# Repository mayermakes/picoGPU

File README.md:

# picoGPU
RPi pico used as crude Graphics adapter (only low res text mode)

Firmware for RP2040/pico
-> can receive commands via I2C and SERIAL
i2c allows for more screen control ( only works between MCUs for unknown reason)
Serial just prints what it receives to screen and changes to random color for each new page.
Serial works on MCu and SBC/PC

Driver published as python script and compiled binary for Linux (x86_AMD64 and RPI_ARM).
For those asking for a windows exe..... pffffff...lol

Seriously, pray that I never get the urge to publish special exe files. 
Meanwhile you can use a windows machine to compile the python script into an exe.

as seen on Element14 presents 2024
CC-BY-SA mayermakes 2024
 MAYER MAKES in all varaiants are registered trademarks.
Raspberry PI and any other Trademarks belong to their respective owners.

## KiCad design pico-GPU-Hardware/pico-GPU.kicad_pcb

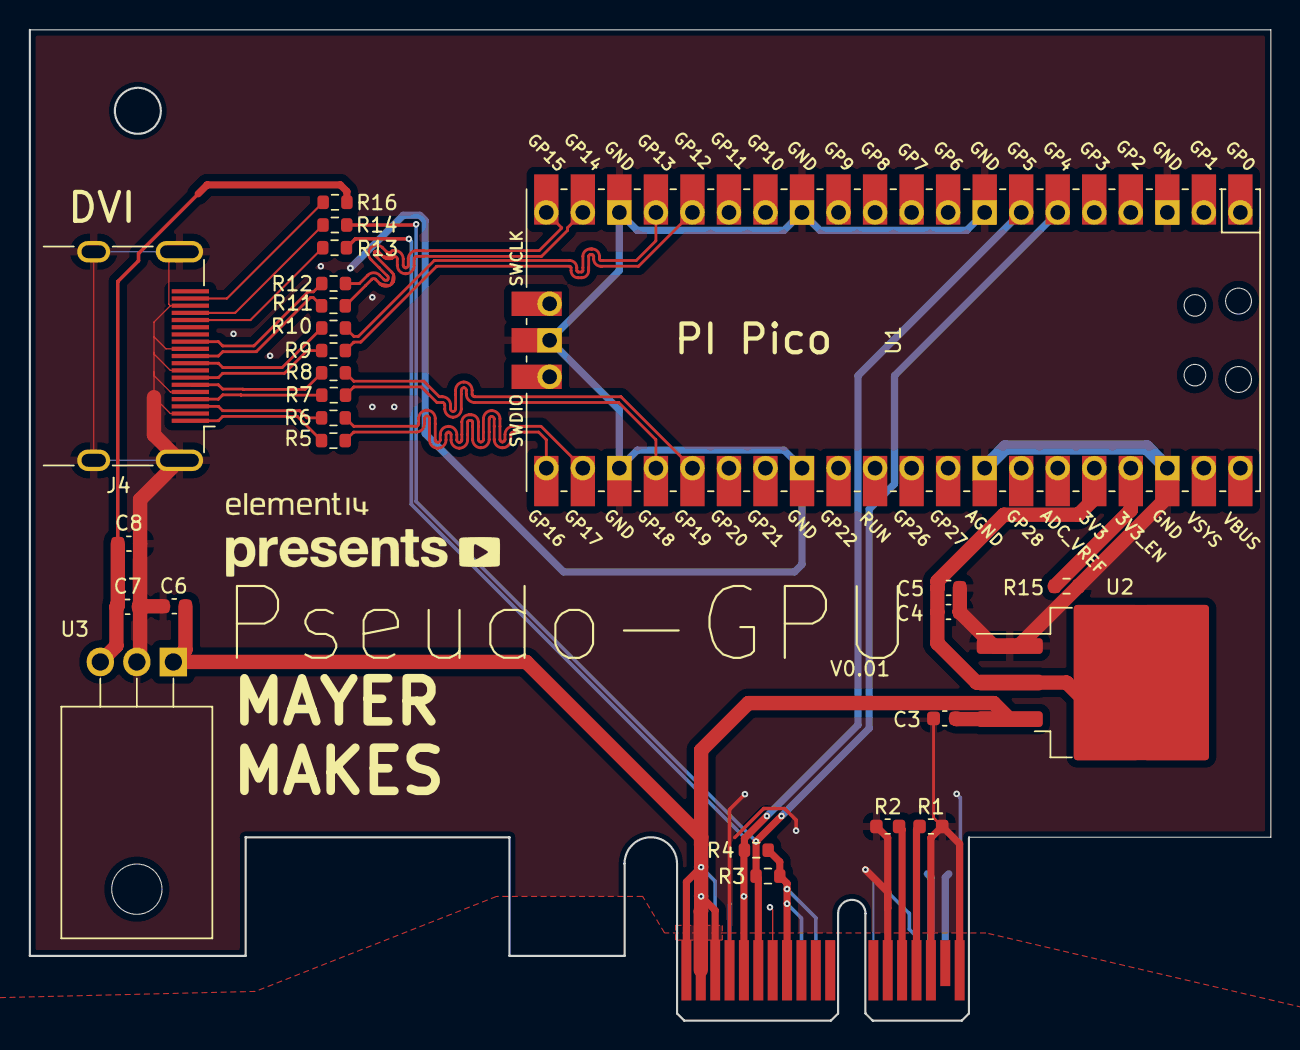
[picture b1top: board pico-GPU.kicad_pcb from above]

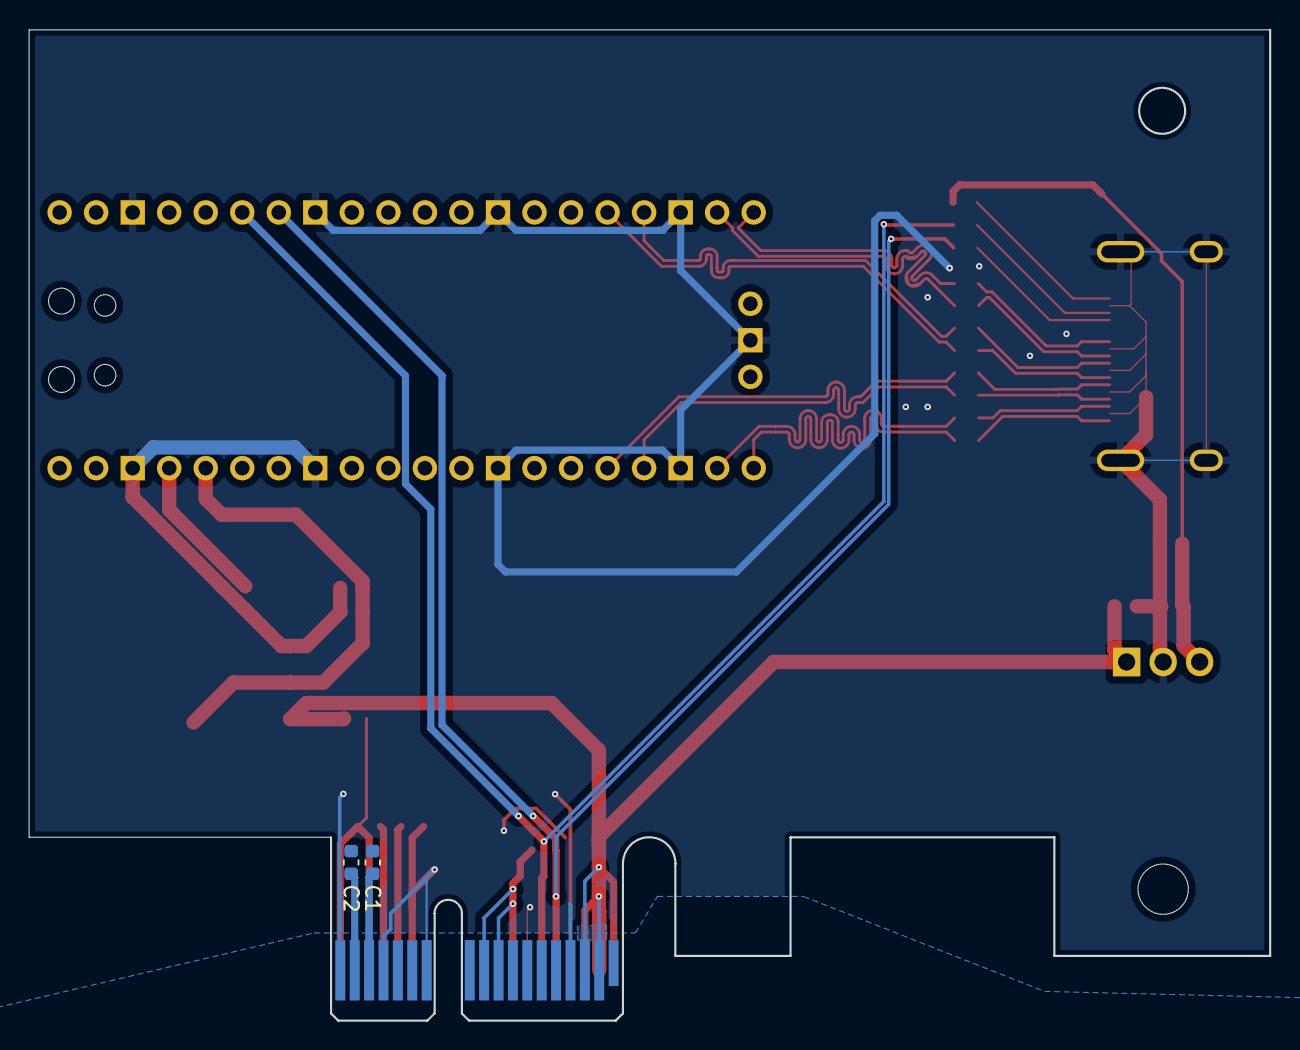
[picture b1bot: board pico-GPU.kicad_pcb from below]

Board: 2 copper layers, 86.2 x 68.9 mm, 31 parts (2 on the bottom side), 31 nets.

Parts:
C1, C2: 100n; C_0603_1608Metric
C3, C4, C6, C7: 10uF; C_0603_1608Metric
C5, C8: 0,1uF; C_0603_1608Metric
J1: PCIexpress_bracket; PCIexpress_bracket_full
J2: PCIexpress_x1
J4: NOT_HDMI_A; HDMI_A_Molex_208658-1001_Horizontal
R1, R2: 49.9; R_0603_1608Metric
R3, R4: 100k; R_0603_1608Metric
R5, R6, R7, R8, R9, R10, R11, R12: 270; R_0603_1608Metric
R13, R14, R15, R16: 0; R_0603_1608Metric
Ref**: Val**; e14presents logo 20mm silk only v1
U1: Pico; RPi_Pico_SMD_TH
U2: LM1085-3.3; TO-263-3_TabPin2
U3: LM7805_TO220; TO-220F-3_Horizontal_TabDown

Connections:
3V3_RAIL: C4.1, C5.1, U1.36 (3V3), U2.2 (VO)
5V_RAIL: C7.1, C8.1, R16.1, U3.3 (VO)
+3V3: J2.A9 (+3.3V), J2.A10 (+3.3V), J2.B8 (+3.3V), R3.1, R4.1
+12V: C3.1, C6.1, J2.A2 (+12V), J2.A3 (+12V), J2.B1 (+12V), J2.B2 (+12V), J2.B3 (+12V), U2.3 (VI), U3.1 (VI)
/CK+: J4.10 (CK+), R11.2
/CK-: J4.12 (CK-), R12.2
/D0+: J4.7 (D0+), R9.2
/D0-: J4.9 (D0-), R10.2
/D1+: J4.4 (D1+), R7.2
/D1-: J4.6 (D1-), R8.2
/D2+: J4.1 (D2+), R5.2
/D2-: J4.3 (D2-), R6.2
/PCIexpress_connector/_PER0_N: C2.1, J2.A17 (PERn0)
/PCIexpress_connector/_PER0_P: C1.2, J2.A16 (PERp0)
/PET0_N: J2.B15 (PETn0), R1.1
/PET0_P: J2.B14 (PETp0), R2.1
/PICO_CK+: R11.1, U1.19 (GPIO14)
/PICO_CK-: R12.1, U1.20 (GPIO15)
/PICO_D0+: R9.1, U1.16 (GPIO12)
/PICO_D0-: R10.1, U1.17 (GPIO13)
/PICO_D1+: R7.1, U1.24 (GPIO18)
/PICO_D1-: R8.1, U1.25 (GPIO19)
/PICO_D2+: R5.1, U1.21 (GPIO16)
/PICO_D2-: R6.1, U1.22 (GPIO17)
/SMCLK: J2.B5 (SMCLK), R4.2, R13.1, U1.7 (GPIO5)
/SMDAT: J2.B6 (SMDAT), R3.2, R14.1, U1.6 (GPIO4)
GND: C3.2, C4.2, C5.2, C6.2, C7.2, C8.2, J2.A4 (GND), J2.A12 (GND), J2.A15 (GND), J2.A18 (GND), J2.B4 (GND), J2.B7 (GND), J2.B13 (GND), J2.B16 (GND), J2.B18 (GND), J4.2 (D2S), J4.5 (D1S), J4.8 (D0S), J4.11 (CKS), J4.17 (GND), J4.SH, R1.2, R2.2, R15.2, U1.3 (GND), U1.8 (GND), U1.13 (GND), U1.18 (GND), U1.23 (GND), U1.28 (GND), U1.33 (AGND), U1.38 (GND), U1.42 (GND), U2.1 (GND), U3.2 (GND)
unnamed: J4.18 (+5V), R16.2
unnamed: J4.15 (SCL), R13.2
unnamed: J4.16 (SDA), R14.2
unnamed: R15.1, U1.37 (3V3_EN)

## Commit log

2024-06-26 Update LICENSE
2024-06-26 initial version - likely with a lot of bugs
    only text mode for now
    white text on coloured(selectable) background
    standalone /pipelined usage
    usable as python module within other python scripts
    untested
2024-06-26 hard and software for pico GPU
    as seen on E14 presents
2024-06-27 USB input version
    I2c works only with messages coming form another MCu (ESP, RP2040/pic, Arduino, AVR) so far.
    USB works for Computers/SBC like Raspberry Pi /lattepanda or PC
2024-06-27 Delete GPUdriver directory
    Completely replaced with a USB version
2024-06-27 Working version.
    Interactive mode prints whatever you type onto a display
    Or you can pipline programs and files into this to redirect the output .
2024-06-29 Delete usbGPUdriver/dist/usbGPUdriver directory
    will bereplaced
2024-06-29 Delete usbGPUdriver/build/usbGPUdriver directory
    will be replaced
2024-06-29 Delete usbGPUdriver/usbGPUdriver.spec
    will be replaced
2024-06-29 Compiled versions
    for X86_AMD64 and Raspberry Pi_ARM
    to run the folder structure must be retained.
    the binary is in dist. you can pipeline into it or just type when it runs to push the output on every NewLine
    the python version is for usage as a python module
